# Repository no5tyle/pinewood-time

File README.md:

# pinewood-time

A pinewood derby race timer built on a Raspberry Pi Pico: a circuit board you solder the Pico to, with
everything a timer needs, the firmware for it, and a 3D-printed finish gate that clamps onto the track and
holds the board and a break-beam sensor for each lane.

- **Up to 4 lanes a gate**, timed to the microsecond from the start gate opening (results to 0.0001 s)
- **Tracks side by side race as one heat:** link up to three finish gates (up to 12 lanes). Every gate is the same and works on its own too; linked, each times its own track from its own start gate and the first one reports the whole heat ([how](docs/wiring.md#linking-gates))
- **PDT-compatible**: talks the protocol of the PDT timer over USB, so race software with a PDT option can drive it
- Start gate and reset button inputs; in the gate, an MX keyboard switch is the button. It can instead call
  up the next heat in the race software (a serial message, and a key press on the timer's USB keyboard)
- Optional per-lane 7-segment displays (I2C), showing a running clock, then each car's time and place
- RGB status light; sensor test mode; settings saved in flash
- All through-hole parts, 49 of them, hand-solderable; powered from the USB cable (a USB-C socket on the gate)
- Works with [Pinewood Control](https://github.com/no5tyle/pinewood-control), whose optional timer add-on fills in
  each heat's finish order and shows the times on the kiosk

> **Status:** the board passes KiCad's design rule check and the firmware builds and passes its tests, but
> no board has been made and tested yet. Build one at your own risk, and please open an issue with what you find.

## What's here

| | |
|---|---|
| [`dist/`](dist) | Firmware ready to flash: `pinewood-time-pico.uf2` (Pico, RP2040) and `pinewood-time-pico2.uf2` (Pico 2, RP2350) |
| [`hardware/fab/pinewood-time-gerbers.zip`](hardware/fab/pinewood-time-gerbers.zip) | Gerbers and drill files: upload this to a board maker |
| [`hardware/fab/bom.md`](hardware/fab/bom.md) | Parts list (also [`bom.csv`](hardware/fab/bom.csv)) |
| [`docs/wiring.md`](docs/wiring.md) | Wiring the sensors, gate, button and displays |
| [`docs/build-guide.pdf`](docs/build-guide.pdf) | The whole build as a printable guide: parts (Core Electronics and AliExpress), ordering the board, soldering, printing the gate, the track change, final assembly, testing |
| [`docs/kit-3-lane.md`](docs/kit-3-lane.md) | A 3-lane kit: shopping list (Australia), what to solder, wiring, setup |
| [`docs/protocol.md`](docs/protocol.md) | The serial protocol and settings commands |
| [`docs/schematic.svg`](docs/schematic.svg) | The circuit |
| [`firmware/`](firmware) | Firmware source (C, Pico SDK) and host tests |
| [`hardware/`](hardware) | The board, generated by script with KiCad 7 |
| [`hardware/gate/`](hardware/gate) | A 3D-printed finish gate: houses the timer and the lane sensors, with an MX key for the button |

## The board

Long and narrow (178 × 28 mm) so it fits inside the gate's beam. Lanes 1 to 4 run along the left, each a
socket with three upright resistors above it; then LINK IN and LINK OUT, for joining gates, and the link's
power diode; then the start gate, reset, display and spare-pin connectors, the status light, and the Pico at
the right-hand end with its USB socket just past the end of the board. (Board v1.1 had eight lane sockets
and no links; the firmware still runs it.)

## The finish gate

From the top: the MX key and the **top cover** (with the status light's lens), the **timer board** lying in
the beam, the two **gate halves** (joined at the beam, between lanes 1 and 2), the **receivers** that sit in
the pods under the beam, the **USB-C socket** on the right leg, and under the track the **sensor bar**,
which holds the emitters in the rails and dovetails up into both legs. All of it prints without supports;
the files and settings are in [`hardware/gate`](hardware/gate).

## 1. Order the board

Upload `hardware/fab/pinewood-time-gerbers.zip` to JLCPCB, PCBWay or similar. Settings: 2 layers,
178 × 28 mm, 1.6 mm thick, any colour, HASL (lead-free or not) is fine. Everything else at the defaults.
The board is long and narrow so it fits inside the [finish gate](hardware/gate)'s beam.

## 2. Get the parts

See [the parts list](hardware/fab/bom.md). In short, per board:

- a Raspberry Pi Pico (or Pico 2), and 2 × 20-pin 2.54 mm male headers if yours hasn't got them
- 1/4 W resistors: 4 × 180 Ω, 8 × 10k, 10 × 1k, 2 × 4.7k, 3 × 220 Ω
- capacitors: 100 µF 10 V electrolytic (6.3 mm, 2.5 mm pitch), 100 nF ceramic (5 mm pitch)
- JST XH sockets: 6 × 4-pin (B4B-XH-A: 4 lanes and 2 links), 2 × 2-pin (B2B-XH-A), and matching plugs and crimps for your cables
- a 1N5817 Schottky diode (for linking gates)
- 1 × 4 and 1 × 6 2.54 mm pin headers, a 5 mm common-cathode RGB LED
- a button for the RESET socket: the gate's MX key, or any push-to-make button on a cable

And for the track: a sensor per lane, a start gate switch, optionally a remote reset button and
displays. See [wiring](docs/wiring.md).

You only need to fit as many lane sockets and resistor sets as you have lanes, and the links (J13, J14, R41-R46,
D2) only to join gates.

## 3. Solder it

The resistors stand upright, three to a lane, with their values printed above them. Lowest parts first:
the ceramic capacitor, the resistors (body down into the circle, the bent-over lead in the other hole),
then the LED (its longest leg, the common cathode, goes in the second hole), the electrolytic capacitor
(+ to the square pad), the pin headers and JST sockets (turned to match their outlines on the board), and
the Pico last.

The Pico goes at the right-hand end with its USB socket just past the end of the board, either on pin
headers (so it can be swapped) or flat on its castellated edges. Inside the gate, solder it flat or on
short (2.5 mm) headers, so there's room above it for the MX key.

## 4. Flash the firmware

Hold the Pico's BOOTSEL button while plugging it in; it shows up as a drive called RPI-RP2 (or RP2350).
Copy the `.uf2` for your Pico onto it. It restarts as the timer: the status light blinks amber.

## 5. Assemble the gate

The board lies on two ledges inside the beam's right half, under the cover, with the Pico's USB going
into the right leg:

Each lane's emitter lies flat in the sensor bar under the track, looking up through a turret that comes up
into a 10 mm hole in the rail at the finish line; its receiver looks down from a pod under the beam. The
only change to the track is those three holes:

The sensor bar runs under the board from leg to leg and locks into both, so the gate clamps onto the track
with nothing screwed to it:

A panel-mount USB-C socket on the right leg makes it one unit: plug in any USB-C cable.

The step-by-step assembly, with the screws for each step, is in the [build guide](docs/build-guide.pdf)
and the [gate's notes](hardware/gate/README.md#assembly).

## 6. Set it up

Plug it into the race computer. It appears as a serial port (COM*n* on Windows, `/dev/ttyACM0` on Linux,
`/dev/cu.usbmodem…` on a Mac). In a serial terminal, or the race software's console:

```
#lanes 4
#save
```

Then hold reset while plugging in to check each sensor in [test mode](docs/protocol.md#test-mode), and
choose the PDT timer in your race software.

## Build it yourself

### Firmware

Needs the [Pico SDK](https://github.com/raspberrypi/pico-sdk) (2.1 or later), CMake and `arm-none-eabi-gcc`.

```bash
cmake -S firmware -B firmware/build -DPICO_SDK_PATH=/path/to/pico-sdk -DPICO_BOARD=pico
```

```bash
cmake --build firmware/build
```

Use `-DPICO_BOARD=pico2` for the Pico 2. The timer's logic is in `firmware/src/timer_core.c`, kept free of
hardware so it can be tested on a computer:

```bash
make -C firmware/test
```

GitHub Actions runs the tests and builds both UF2s on every push.

### Board

The board is a script, not a hand-drawn layout: `hardware/generate_board.py` holds every part, where it
goes and what it connects to. `hardware/build.sh` places the parts, routes the tracks with a small router of
its own (`hardware/route.py`), adds the ground pours, runs KiCad's design rule check (stopping on any error),
then writes the Gerbers, drill files, parts list, schematic and pictures. It needs KiCad 7 (its Python module
and `kicad-cli`), and Node with Playwright for the pictures (`SKIP_RENDERS=1` skips them).

```bash
hardware/build.sh
```

The result, `hardware/pinewood-time.kicad_pcb`, opens in KiCad for anyone who'd rather edit it by hand.

## Licence

MIT, see [LICENSE](LICENSE). The PDT protocol support is an independent implementation written for
compatibility; this project contains no code or design files from the PDT, and isn't connected with it.

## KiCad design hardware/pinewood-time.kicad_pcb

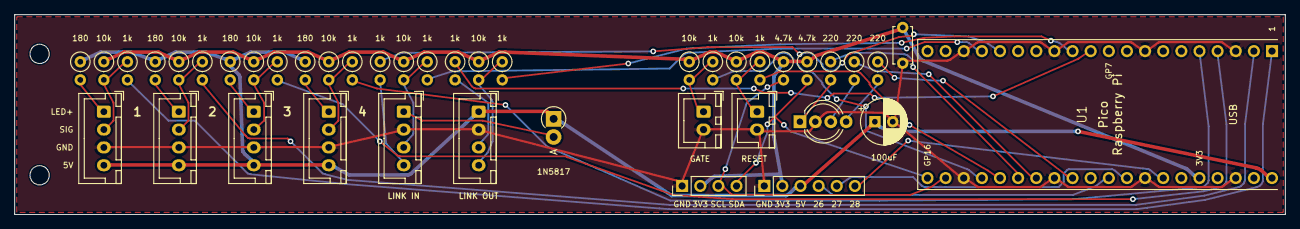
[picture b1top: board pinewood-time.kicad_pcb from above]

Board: 2 copper layers, 178.0 x 28.0 mm, 44 parts (0 on the bottom side), 39 nets.

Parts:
C1: 100uF 10V; CP_Radial_D6.3mm_P2.50mm
C2: 100nF; C_Disc_D5.0mm_W2.5mm_P5.00mm
D1: RGB; LED_D5.0mm-4_RGB_Wide_Pins
D2: 1N5817; D_DO-41_SOD81_P2.54mm_Vertical_AnodeUp
H1, H2: M2.5; MountingHole_2.7mm_M2.5
J1: LANE 1; JST_XH_B4B-XH-A_1x04_P2.50mm_Vertical
J2: LANE 2; JST_XH_B4B-XH-A_1x04_P2.50mm_Vertical
J3: LANE 3; JST_XH_B4B-XH-A_1x04_P2.50mm_Vertical
J4: LANE 4; JST_XH_B4B-XH-A_1x04_P2.50mm_Vertical
J9: GATE; JST_XH_B2B-XH-A_1x02_P2.50mm_Vertical
J10: RESET; JST_XH_B2B-XH-A_1x02_P2.50mm_Vertical
J11: DISPLAYS; PinHeader_1x04_P2.54mm_Vertical
J12: AUX; PinHeader_1x06_P2.54mm_Vertical
J13: LINK IN; JST_XH_B4B-XH-A_1x04_P2.50mm_Vertical
J14: LINK OUT; JST_XH_B4B-XH-A_1x04_P2.50mm_Vertical
R1, R2, R3, R4: 180; R_Axial_DIN0207_L6.3mm_D2.5mm_P2.54mm_Vertical
R11, R12, R13, R14, R31, R33, R42, R45: 10k; R_Axial_DIN0207_L6.3mm_D2.5mm_P2.54mm_Vertical
R21, R22, R23, R24, R32, R34, R41, R43, R44, R46: 1k; R_Axial_DIN0207_L6.3mm_D2.5mm_P2.54mm_Vertical
R35, R36: 4.7k; R_Axial_DIN0207_L6.3mm_D2.5mm_P2.54mm_Vertical
R37, R38, R39: 220; R_Axial_DIN0207_L6.3mm_D2.5mm_P2.54mm_Vertical
U1: Raspberry Pi Pico; RaspberryPi_Pico

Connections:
+3V3: C2.1, J11.2, J12.2, R11.1, R12.1, R13.1, R14.1, R31.1, R33.1, R35.1, R36.1, R42.1, R45.1, U1.36
AUX1: J12.4, U1.31
AUX2: J12.5, U1.32
AUX3: J12.6, U1.34
GATE: J9.1, R31.2, R32.1
GATE_IN: R32.2, U1.24
GND: C1.2, C2.2, D1.2, J1.3, J2.3, J3.3, J4.3, J9.2, J10.2, J11.1, J12.1, J13.2, J14.2, U1.3, U1.8, U1.13, U1.18, U1.23, U1.28, U1.33, U1.38
IN_RX: R43.2, U1.17
IN_RX_C: J13.3, R42.2, R43.1
IN_TX: R41.1, U1.16
IN_TX_C: J13.4, R41.2
LANE1: R21.2, U1.1
LANE2: R22.2, U1.2
LANE3: R23.2, U1.4
LANE4: R24.2, U1.5
LED1: J1.1, R1.2
LED2: J2.1, R2.2
LED3: J3.1, R3.2
LED4: J4.1, R4.2
LED_B: D1.4, R39.2
LED_B_IN: R39.1, U1.29
LED_G: D1.3, R38.2
LED_G_IN: R38.1, U1.27
LED_R: D1.1, R37.2
LED_R_IN: R37.1, U1.26
LINK_5V: D2.2, J13.1
OUT_RX: R46.2, U1.12
OUT_RX_C: J14.4, R45.2, R46.1
OUT_TX: R44.1, U1.11
OUT_TX_C: J14.3, R44.2
RESET: J10.1, R33.2, R34.1
RESET_IN: R34.2, U1.25
SCL: J11.3, R35.2, U1.22
SDA: J11.4, R36.2, U1.21
SENSE1: J1.2, R11.2, R21.1
SENSE2: J2.2, R12.2, R22.1
SENSE3: J3.2, R13.2, R23.1
SENSE4: J4.2, R14.2, R24.1
VBUS: C1.1, D2.1, J1.4, J2.4, J3.4, J4.4, J12.3, J14.1, R1.1, R2.1, R3.1, R4.1, U1.40

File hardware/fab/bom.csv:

Qty,References,Value,Description,Footprint,Part number,LCSC
1,U1,Raspberry Pi Pico,"Raspberry Pi Pico (RP2040) or Pico 2 (RP2350), on 2x20 pin headers or soldered flat",RaspberryPi_Pico,SC0915,
6,J1 J2 J3 J4 J13 J14,B4B-XH-A,"Lane sensor socket, JST XH 4-pin, 2.5 mm; Link In socket (to the main gate), JST XH 4-pin, 2.5 mm; Link Out socket (to the next gate), JST XH 4-pin, 2.5 mm",JST_XH_B4B-XH-A_1x04_P2.50mm_Vertical,JST B4B-XH-A,C144395
4,R1 R2 R3 R4,180,"IR emitter current limit, 1/4 W (about 20 mA at 5 V)",R_Axial_DIN0207_L6.3mm_D2.5mm_P2.54mm_Vertical,,
8,R11 R12 R13 R14 R42 R45 R31 R33,10k,"Sensor pull-up to 3.3 V, 1/4 W; Link in: pull-up, data in (idle when unplugged), 1/4 W; Link out: pull-up, data in (idle when unplugged), 1/4 W; Gate pull-up to 3.3 V, 1/4 W; Reset pull-up to 3.3 V, 1/4 W",R_Axial_DIN0207_L6.3mm_D2.5mm_P2.54mm_Vertical,,
10,R21 R22 R23 R24 R41 R43 R44 R46 R32 R34,1k,"Series protection for the Pico input, 1/4 W; Link in: series protection, data out, 1/4 W; Link in: series protection, data in, 1/4 W; Link out: series protection, data out, 1/4 W; Link out: series protection, data in, 1/4 W; Series protection, 1/4 W",R_Axial_DIN0207_L6.3mm_D2.5mm_P2.54mm_Vertical,,
1,D2,1N5817,"Power in from the link: Schottky 1N5817, 1 A (stripe = cathode, to 5V)",D_DO-41_SOD81_P2.54mm_Vertical_AnodeUp,1N5817,C2480
2,J9 J10,B2B-XH-A,"Start gate switch socket, JST XH 2-pin; Reset button socket (the gate's MX key), JST XH 2-pin",JST_XH_B2B-XH-A_1x02_P2.50mm_Vertical,JST B2B-XH-A,C158012
2,R35 R36,4.7k,"I2C pull-up, 1/4 W",R_Axial_DIN0207_L6.3mm_D2.5mm_P2.54mm_Vertical,,
3,R37 R38 R39,220,"Status light, red, 1/4 W; Status light, green, 1/4 W; Status light, blue, 1/4 W",R_Axial_DIN0207_L6.3mm_D2.5mm_P2.54mm_Vertical,,
1,J11,1x04 header,"I2C header for lane displays (HT16K33 4-digit backpacks, address 0x70 + lane - 1), 1x4 2.54 mm",PinHeader_1x04_P2.54mm_Vertical,,
1,J12,1x06 header,"Spare pins: GND, 3V3, 5V (powers the gate's track emitters), GP26, GP27, GP28, 1x6 2.54 mm",PinHeader_1x06_P2.54mm_Vertical,,
1,D1,RGB,"Status light, 5 mm RGB LED, common cathode, pins R-K-G-B (cathode longest)",LED_D5.0mm-4_RGB_Wide_Pins,,
1,C1,100uF 10V,"5 V supply bulk, electrolytic, 6.3 mm, 2.5 mm pitch",CP_Radial_D6.3mm_P2.50mm,,
1,C2,100nF,"3.3 V decoupling, ceramic, 5 mm pitch",C_Disc_D5.0mm_W2.5mm_P5.00mm,,

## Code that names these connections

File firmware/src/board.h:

/*
 * The pinewood-time board's wiring: which Pico pin does what. Matches hardware/ (the PCB) and
 * docs/wiring.md. Lanes are on the Pico's left-hand pins, everything else on the right.
 */
#ifndef PT_BOARD_H
#define PT_BOARD_H

/* Lane finish sensors: lane 1 on GP0 to lane 8 on GP7, so they all read in one go. Boards from v1.2 have
 * sockets for lanes 1 to 4 (more lanes come from linked gates); v1.1 boards have all eight */
#define PIN_LANE_FIRST 0

#define PIN_I2C_SDA 16 /* lane displays (I2C0) */
#define PIN_I2C_SCL 17
#define PIN_GATE 18    /* start gate switch (gate 1) */
#define PIN_RESET 19   /* reset button (on the board, and the RESET socket) */
#define PIN_LED_R 20   /* status light */
#define PIN_LED_G 21
#define PIN_LED_B 22
/* Spare pins on the AUX header: GP26, GP27, GP28. Start gates 2 to 4 for tracks side by side ("#gate2 4-6"),
 * otherwise free (buzzer, start solenoid driver, ...) */
#define PIN_AUX_1 26
#define PIN_AUX_2 27
#define PIN_AUX_3 28
#define PIN_GATE_2 PIN_AUX_1
#define PIN_GATE_3 PIN_AUX_2
#define PIN_GATE_4 PIN_AUX_3

/* Links to other gates (link.c), on the Pico's two UARTs; unconnected on v1.1 boards.
 * LINK IN (towards the main gate) on UART0, LINK OUT (towards the next gate) on UART1 */
#define PIN_LINK_IN_TX 12
#define PIN_LINK_IN_RX 13
#define PIN_LINK_OUT_TX 8
#define PIN_LINK_OUT_RX 9
#define LINK_BAUD 115200

/* Lane displays: HT16K33 4-digit LED backpacks, lane 1 at 0x70 to lane 8 at 0x77 */
#define DISPLAY_ADDR_FIRST 0x70

#endif
